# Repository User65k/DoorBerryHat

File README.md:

# DoorBerry
Use a Raspberry Pi as a VoIP door intercom system.

I use it with my FritzBox to alert all my DECT Phones.
Tested on a Pi 2B+ and a Pi Zero with raspbian (and mono).

## Software

Please find it [here](https://github.com/User65k/DoorBerryServer).

## Hardware

All Files are creaded with [KiCad](http://kicad.org/).

### Old Door system

The new System replaces the indoor part of a RITTO intercom system. The Door itself and the other appartments where not modified.

The old system had a fairly simple circut:

### New Door Intercom

The system is replaced by a Raspberry with a custum Hat (utilizing the GPIOs of the Pi).
Bell and Buzzer can operate independently from the new system (in case of Network errors, Bugs, :speak_no_evil:).

The switch (SW1) can open the door regardless of any errors in the Pi.

The speaker (SP1) will notify about someone ringing the Bell independently from the Pi.

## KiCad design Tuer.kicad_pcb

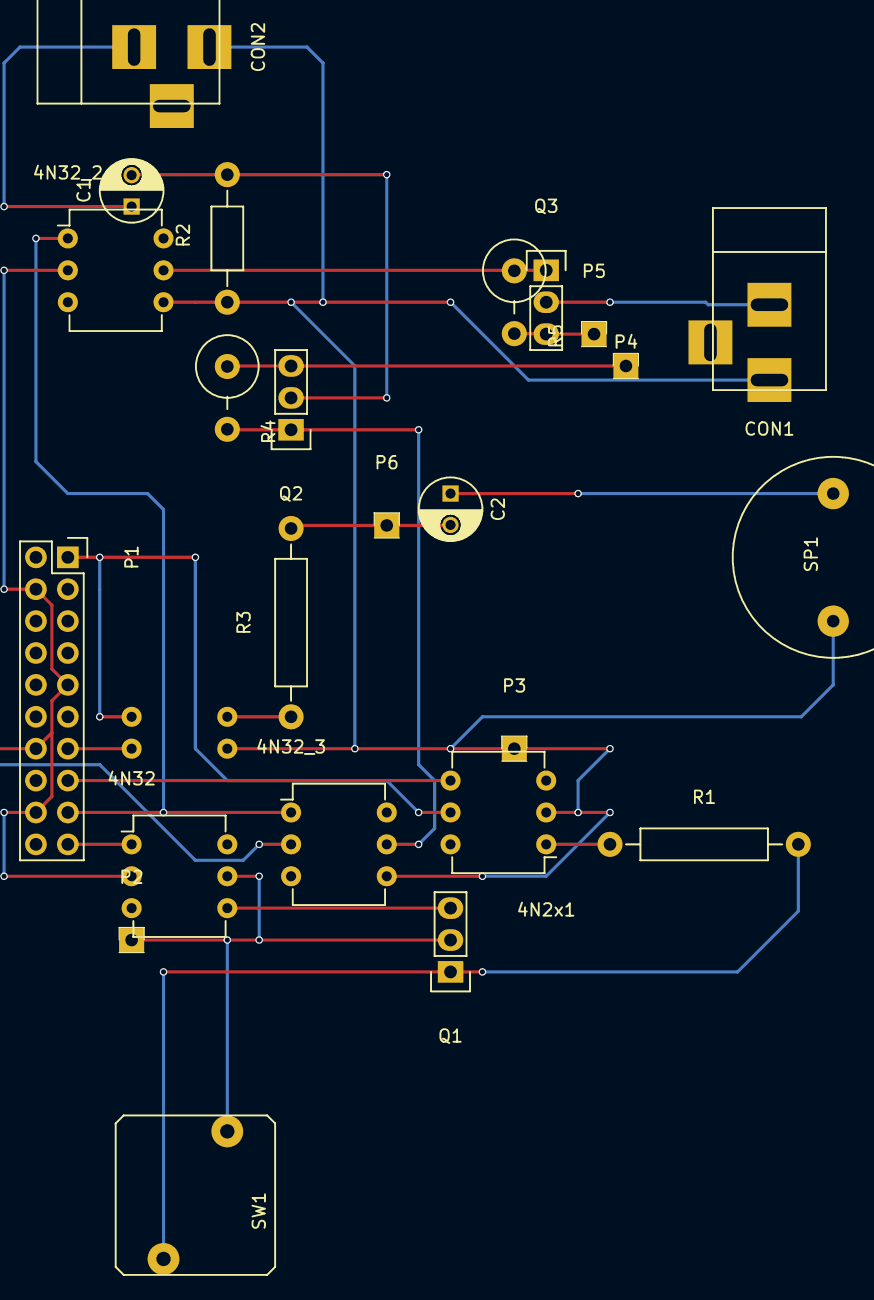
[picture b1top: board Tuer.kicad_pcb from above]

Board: 2 copper layers, 25 parts (1 on the bottom side), 21 nets.

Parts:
4N2x1: isOpen; DIP-6_W7.62mm
4N32: SWOpenDoor; DIP-6_W7.62mm
4N32_2: SWRot; DIP-6_W7.62mm
4N32_3: SWWeis; DIP-6_W7.62mm
C1, C2: 10uF; C_Radial_D5_L6_P2.5
CON1: Sound Out; BARREL_JACK
CON2: Speach In; BARREL_JACK
KB817: IsRing; DIP-4_W7.62mm
P1: Rasp17_36; Socket_Strip_Straight_2x10
P2: Blau; Pin_Header_Straight_1x01
P3: Braun; Pin_Header_Straight_1x01
P4: Weis; Pin_Header_Straight_1x01
P5: Rot; Pin_Header_Straight_1x01
P6: Orange; Pin_Header_Straight_1x01
Q1: BD433; Pin_Header_Straight_1x03
Q2, Q3: Q_PMOS_GDS; Pin_Header_Straight_1x03
R1: 263; Resistor_Horizontal_RM15mm
R2: 56; Resistor_Horizontal_RM10mm
R3: 56; Resistor_Horizontal_RM15mm
R4, R5: 10k; Resistor_Vertical_RM5mm
SP1: SPEAKER; BUZZER
SW1: SW_PUSH

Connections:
+3V3: 4N2x1.5, KB817.4, P1.1
/11V: P5.1, Q3.3, R5.2
/12V: P4.1, Q2.3, R4.1
/23,5V: 4N32.5, P2.1, Q1.2, SW1.1
ActivateMic: 4N32_2.1, 4N32_3.1, P1.17
DetectOpen: 4N2x1.4, P1.15
DetectRing: KB817.3, P1.13
Earth: 4N2x1.2, 4N32_2.4, 4N32_3.4, CON1.1, CON2.1, KB817.2, P3.1, R2.1, SP1.1
GND: 4N32.2, 4N32_2.2, 4N32_3.2, P1.4, P1.9, P1.14, P1.18
unnamed: 4N2x1.1, R1.1
unnamed: 4N32.4, Q1.3
unnamed: 4N32_2.5, Q3.1, R5.1
unnamed: 4N32_3.5, Q2.1, R4.2
unnamed: C1.1, CON2.2
unnamed: C1.2, Q2.2, R2.2
unnamed: C2.1, SP1.2
unnamed: C2.2, P6.1, R3.2
unnamed: CON1.2, Q3.2
unnamed: KB817.1, R3.1
unnamed: Q1.1, R1.2, SW1.2
OpenDoor: 4N32.1, P1.19

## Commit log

2017-12-16 Docu old System
2017-12-16 added circut
2021-06-21 added libs
2021-06-22 hopfully fixed missing libs
2021-11-10 Update README.md
    https://forum.kicad.info/t/warning-avoid-all-links-to-kicad-pcb-org-use-kicad-org/31521
